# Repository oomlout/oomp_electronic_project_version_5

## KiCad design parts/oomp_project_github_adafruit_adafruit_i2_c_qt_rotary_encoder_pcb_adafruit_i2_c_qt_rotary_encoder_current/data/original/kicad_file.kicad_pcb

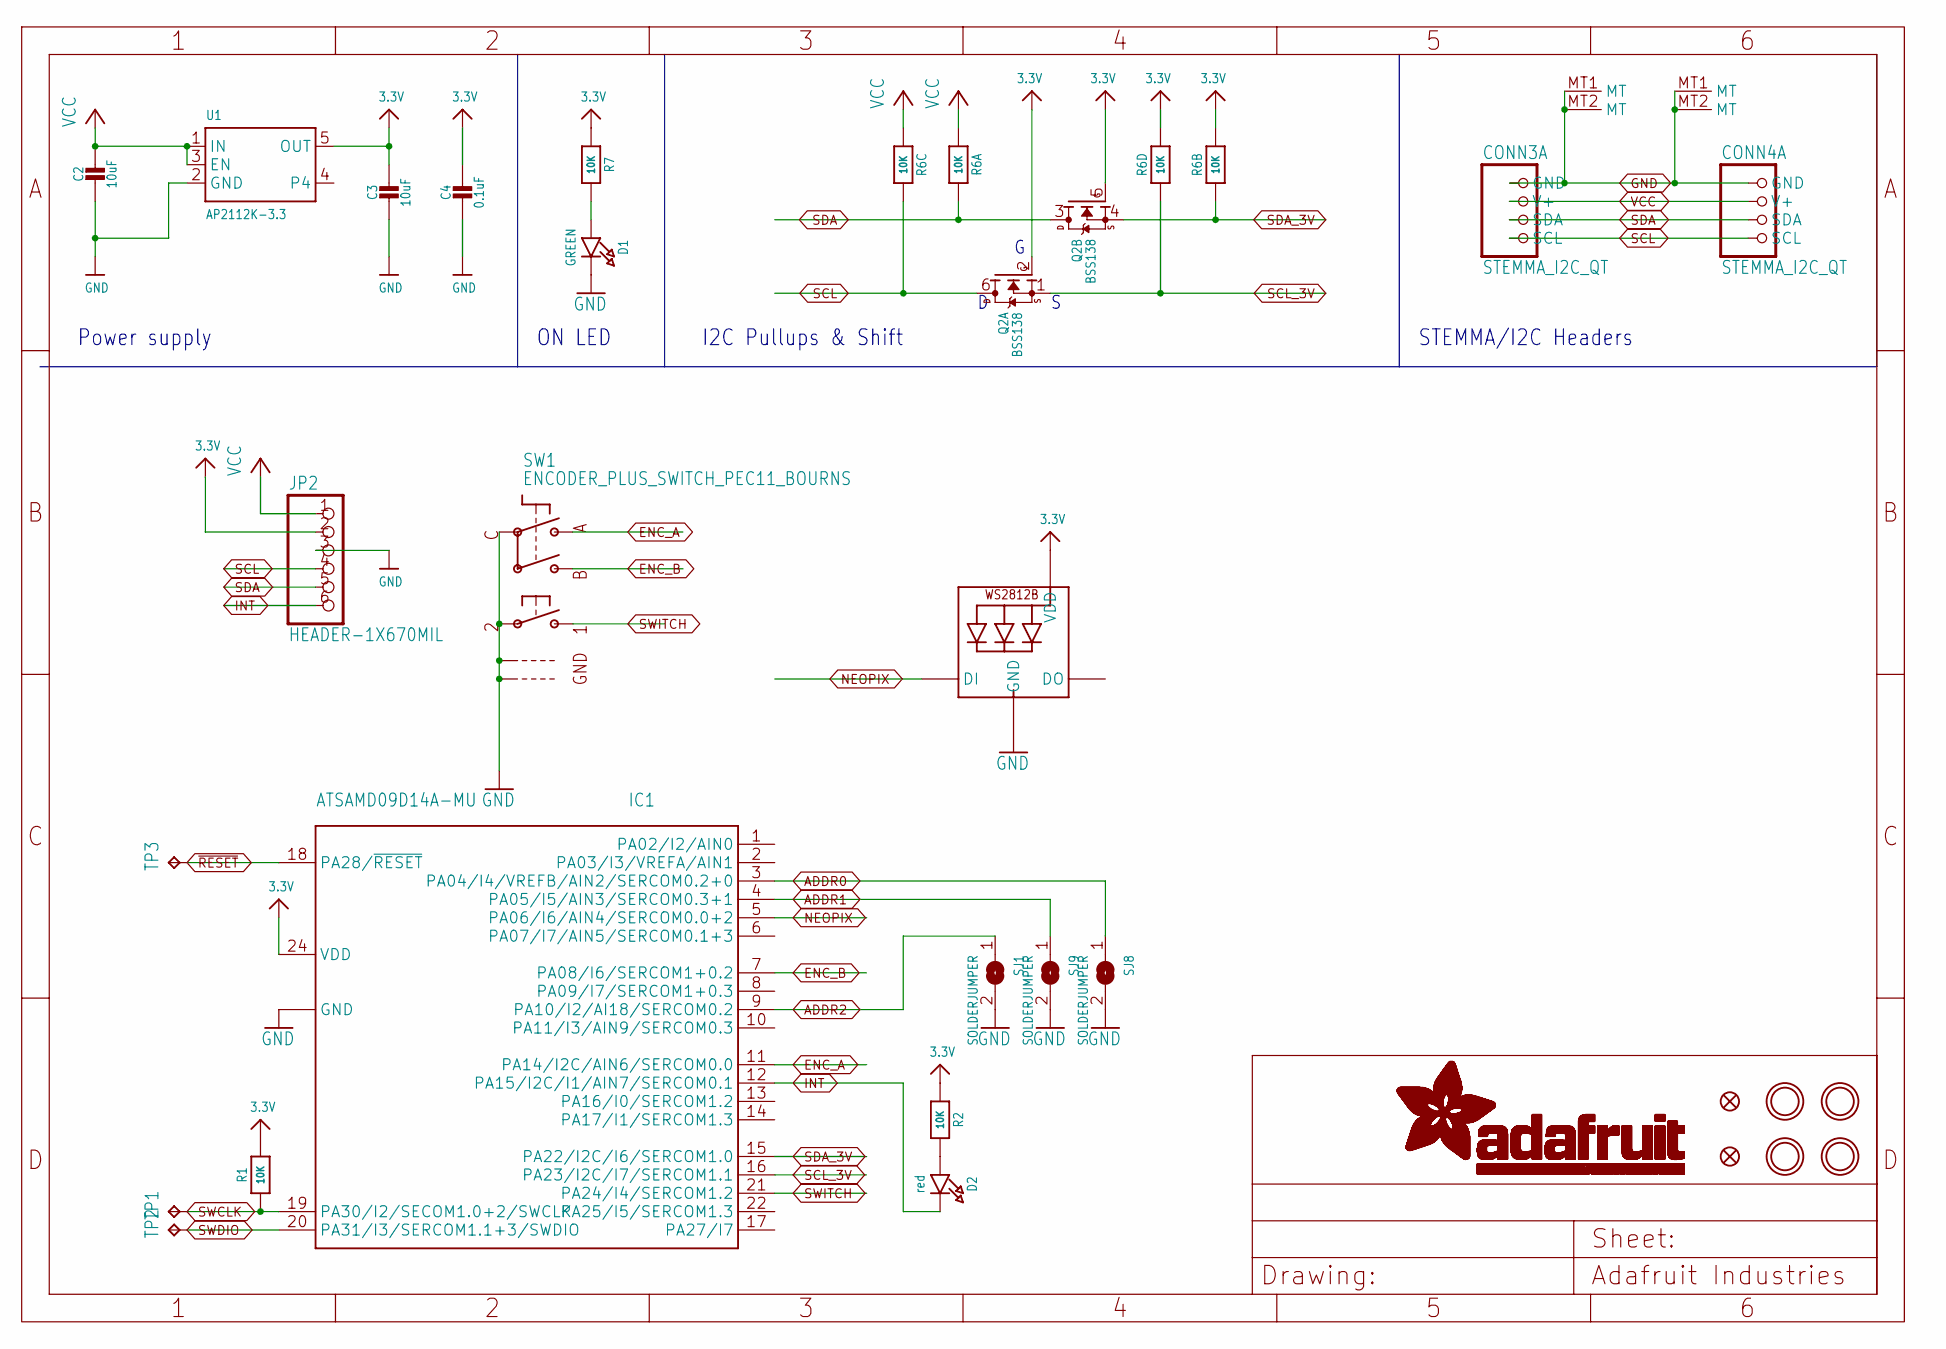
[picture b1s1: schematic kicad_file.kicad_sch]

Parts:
C2, C3: 10uF; 0805-NO
C4: 0.1uF; 0603-NO
CONN3, CONN4: STEMMA_I2C_QT; JST_SH4
D1: GREEN; CHIPLED_0603_NOOUTLINE
D2: red; CHIPLED_0603_NOOUTLINE
FID3, FID4: FIDUCIAL_1MM
IC1: ATSAMD09D14A-MU; QFN24_4MM
JP2: HEADER-1X670MIL; 1X06_ROUND_70
LED1: WS2812B_SK6812E; NEO3535_REVERSE
Q2: BSS138; SOT363
R1, R2, R7: 10K; 0603-NO
R6: 10K; RESPACK_4X0603
SJ1, SJ8, SJ9: SOLDERJUMPER; SOLDERJUMPER_ARROW_NOPASTE
SW1: ENCODER_PLUS_SWITCH_PEC11_BOURNS; PEC11+SWITCH
TP1, TP2, TP3: TPTP15R; TP15R
U1: AP2112K-3.3; SOT23-5
U$25, U$27, U$29, U$30: MOUNTINGHOLE2.5; MOUNTINGHOLE_2.5_PLATED

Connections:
3.3V: C3.1, C4.1, IC1.24 (VDD), JP2.2, LED1.1-VDD (VDD), Q2.2 (G), Q2.5 (G), R1.2, R2.1, R6.2 (1), R6.4 (1), R7.1, U1.5 (OUT)
ADDR0: IC1.3 (PA04/I4/VREFB/AIN2/SERCOM0.2+0), SJ8.1
ADDR1: IC1.4 (PA05/I5/AIN3/SERCOM0.3+1), SJ9.1
ADDR2: IC1.9 (PA10/I2/AI18/SERCOM0.2), SJ1.1
ENC_A: IC1.11 (PA14/I2C/AIN6/SERCOM0.0), SW1.P$A
ENC_B: IC1.7 (PA08/I6/SERCOM1+0.2), SW1.P$B
GND: C2.2, C3.2, C4.2, CONN3.1 (GND), CONN3.MT1 (MT), CONN3.MT2 (MT), CONN4.1 (GND), CONN4.MT1 (MT), CONN4.MT2 (MT), D1.C, IC1.23 (GND), IC1.THERM (GND), JP2.3, LED1.3-GND (GND), SJ1.2, SJ8.2, SJ9.2, SW1.P$2, SW1.P$C, SW1.P$GND1, SW1.P$GND2, U1.2 (GND)
INT: D2.C, IC1.12 (PA15/I2C/I1/AIN7/SERCOM0.1), JP2.6
unnamed: D1.A, R7.2
unnamed: D2.A, R2.2
NEOPIX: IC1.5 (PA06/I6/AIN4/SERCOM0.0+2), LED1.4-DIN (DI)
SCL: CONN3.4 (SCL), CONN4.4 (SCL), JP2.4, Q2.6 (D), R6.6 (2)
SCL_3V: IC1.16 (PA23/I2C/I7/SERCOM1.1), Q2.1 (S), R6.5 (2)
SDA: CONN3.3 (SDA), CONN4.3 (SDA), JP2.5, Q2.3 (D), R6.8 (2)
SDA_3V: IC1.15 (PA22/I2C/I6/SERCOM1.0), Q2.4 (S), R6.7 (2)
SWCLK: IC1.19 (PA30/I2/SECOM1.0+2/SWCLK), R1.1, TP1.TP
SWDIO: IC1.20 (PA31/I3/SERCOM1.1+3/SWDIO), TP2.TP
SWITCH: IC1.21 (PA24/I4/SERCOM1.2), SW1.P$1
VCC: C2.1, CONN3.2 (V+), CONN4.2 (V+), JP2.1, R6.1, R6.3 (1), U1.1 (IN), U1.3 (EN)
~RESET: IC1.18 (PA28/~RESET), TP3.TP

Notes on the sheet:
Power supply
I2C Pullups & Shift
ON LED
STEMMA/I2C Headers

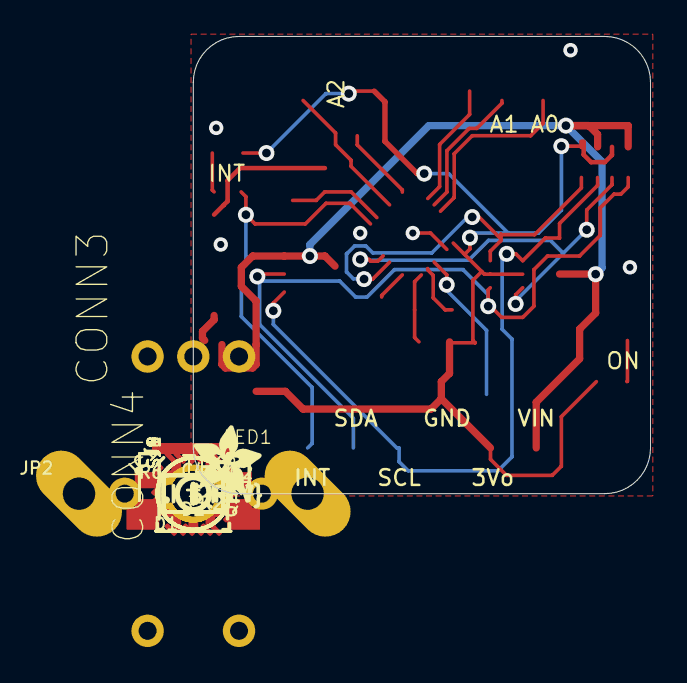
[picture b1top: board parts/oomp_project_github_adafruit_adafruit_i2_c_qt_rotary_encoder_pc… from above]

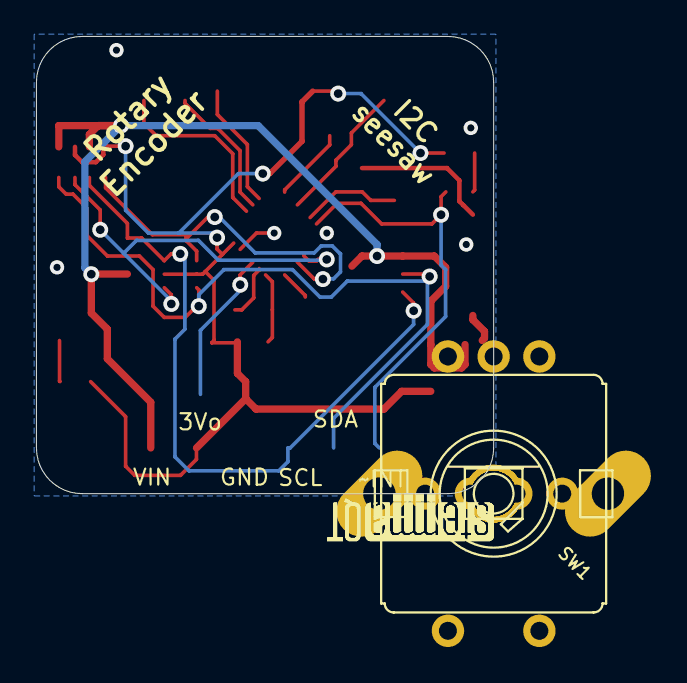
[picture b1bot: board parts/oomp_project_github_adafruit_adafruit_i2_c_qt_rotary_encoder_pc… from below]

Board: 2 copper layers, 25.4 x 25.4 mm, 33 parts (4 on the bottom side), 20 nets.

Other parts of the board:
U$32: ADAFRUIT_3.5MM
U$33: PCBFEAT-REV-040
U$34, U$35: STEMMAQT

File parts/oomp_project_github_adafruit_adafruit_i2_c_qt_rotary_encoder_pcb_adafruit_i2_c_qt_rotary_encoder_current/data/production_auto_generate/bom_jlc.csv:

Comment,Designator,Footprint,LCSC Part #
,JP2,Adafruit I2C QT Rotary Encoder-import-fps:1X06_ROUND_70,C37208
,U$32,Adafruit I2C QT Rotary Encoder-import-fps:ADAFRUIT_3.5MM,
,U$33,Adafruit I2C QT Rotary Encoder-import-fps:PCBFEAT-REV-040,
,"U$34,U$35",Adafruit I2C QT Rotary Encoder-import-fps:STEMMAQT,
0.1uF,C4,Adafruit I2C QT Rotary Encoder-import-fps:0603-NO,C14663
10K,"R1,R2,R7",Adafruit I2C QT Rotary Encoder-import-fps:0603-NO,C98220
10K,R6,Adafruit I2C QT Rotary Encoder-import-fps:RESPACK_4X0603,C98220
10uF,"C2,C3",Adafruit I2C QT Rotary Encoder-import-fps:0805-NO,
AP2112K-3.3,U1,Adafruit I2C QT Rotary Encoder-import-fps:SOT23-5,
ATSAMD09D14A-MU,IC1,Adafruit I2C QT Rotary Encoder-import-fps:QFN24_4MM,
BSS138,Q2,Adafruit I2C QT Rotary Encoder-import-fps:SOT363,
GREEN,D1,Adafruit I2C QT Rotary Encoder-import-fps:CHIPLED_0603_NOOUTLINE,
red,D2,Adafruit I2C QT Rotary Encoder-import-fps:CHIPLED_0603_NOOUTLINE,
STEMMA_I2C_QT,"CONN3,CONN4",Adafruit I2C QT Rotary Encoder-import-fps:JST_SH4,C160404
TPTP15R,"TP1,TP2,TP3",Adafruit I2C QT Rotary Encoder-import-fps:TP15R,
WS2812B_SK6812E,LED1,Adafruit I2C QT Rotary Encoder-import-fps:NEO3535_REVERSE,

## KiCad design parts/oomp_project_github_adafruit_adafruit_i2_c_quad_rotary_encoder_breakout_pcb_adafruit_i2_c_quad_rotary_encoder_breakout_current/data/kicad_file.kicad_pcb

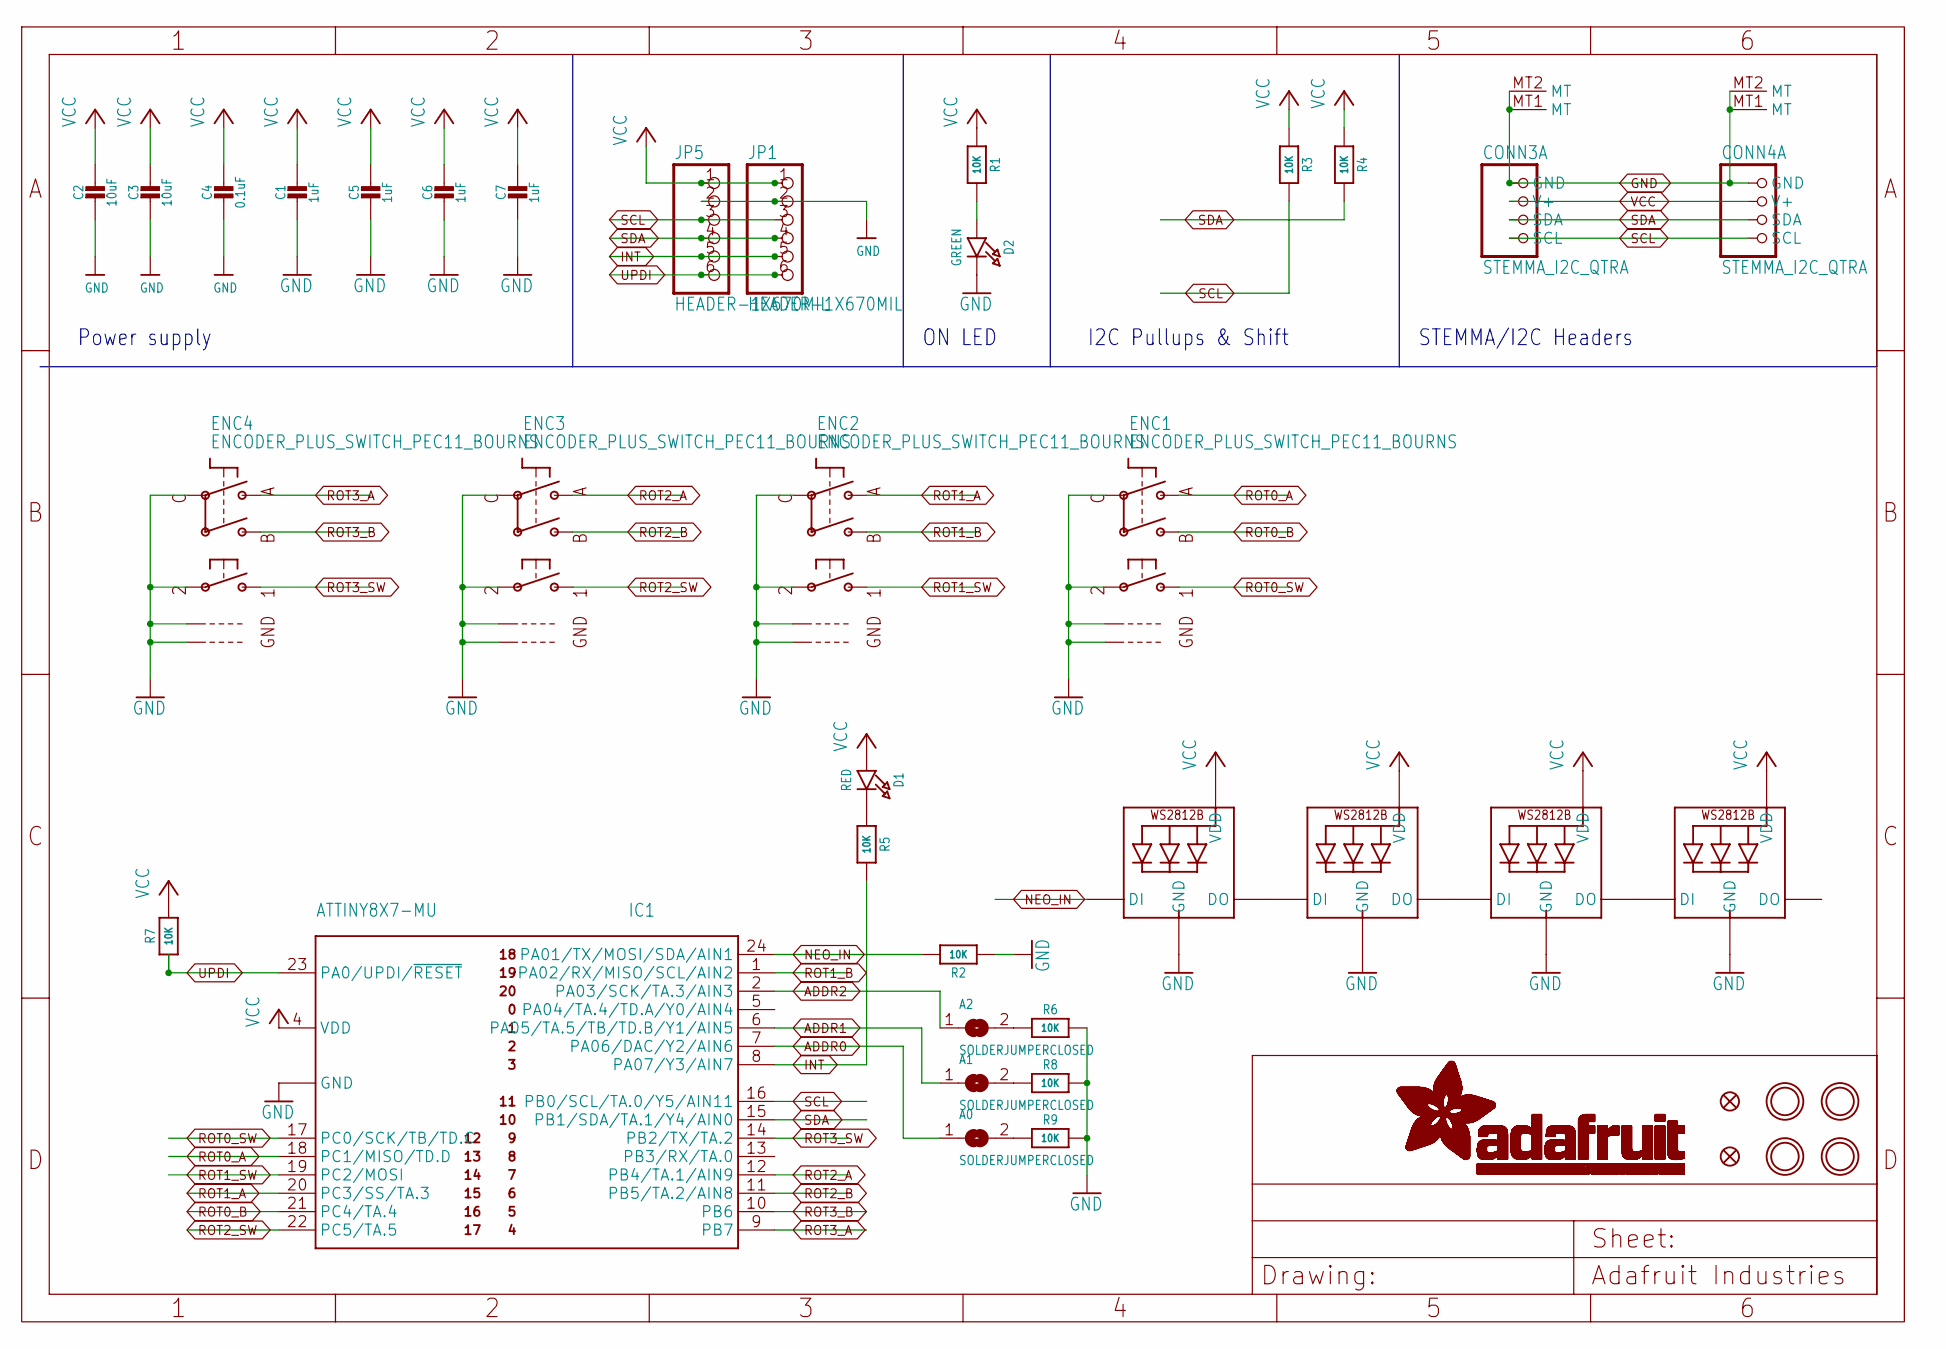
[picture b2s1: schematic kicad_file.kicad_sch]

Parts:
A0, A1, A2: SOLDERJUMPERCLOSED; SOLDERJUMPER_CLOSEDWIRE
C1, C5, C6, C7: 1uF; 0603-NO
C2, C3: 10uF; 0805-NO
C4: 0.1uF; 0603-NO
CONN3, CONN4: STEMMA_I2C_QTRA; JST_SH4_RA; LCSC C145961
D1: RED; CHIPLED_0603_NOOUTLINE
D2: GREEN; CHIPLED_0603_NOOUTLINE
ENC1, ENC2, ENC3, ENC4: ENCODER_PLUS_SWITCH_PEC11_BOURNS; PEC11+SWITCH
FID1, FID2: FIDUCIAL_1MM
IC1: ATTINY8X7-MU; QFN24_4MM
JP1, JP5: HEADER-1X670MIL; 1X06_ROUND_70
LED1, LED2, LED3, LED4: WS2812B_SK6812E; NEO3535_REVERSE
R1, R2, R3, R4, R5, R6, R7, R8, R9: 10K; 0603-NO
U$3, U$17, U$19, U$21: MOUNTINGHOLE2.5; MOUNTINGHOLE_2.5_PLATED

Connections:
ADDR0: A0.1, IC1.7 (PA06/DAC/Y2/AIN6)
ADDR1: A1.1, IC1.6 (PA05/TA.5/TB/TD.B/Y1/AIN5)
ADDR2: A2.1, IC1.2 (PA03/SCK/TA.3/AIN3)
GND: C1.2, C2.2, C3.2, C4.2, C5.2, C6.2, C7.2, CONN3.1 (GND), CONN3.MT1 (MT), CONN3.MT2 (MT), CONN4.1 (GND), CONN4.MT1 (MT), CONN4.MT2 (MT), D2.C, ENC1.P$2, ENC1.P$C, ENC1.P$GND1, ENC1.P$GND2, ENC2.P$2, ENC2.P$C, ENC2.P$GND1, ENC2.P$GND2, ENC3.P$2, ENC3.P$C, ENC3.P$GND1, ENC3.P$GND2, ENC4.P$2, ENC4.P$C, ENC4.P$GND1, ENC4.P$GND2, IC1.3 (GND), IC1.THERM (GND), JP1.2, JP5.2, LED1.3-GND (GND), LED2.3-GND (GND), LED3.3-GND (GND), LED4.3-GND (GND), R2.1, R6.2, R8.2, R9.2
INT: IC1.8 (PA07/Y3/AIN7), JP1.5, JP5.5, R5.2
unnamed: D2.A, R1.2
unnamed: LED1.2-DOUT (DO), LED2.4-DIN (DI)
unnamed: LED2.2-DOUT (DO), LED3.4-DIN (DI)
unnamed: LED3.2-DOUT (DO), LED4.4-DIN (DI)
unnamed: D1.C, R5.1
unnamed: A2.2, R6.1
unnamed: A1.2, R8.1
unnamed: A0.2, R9.1
NEO_IN: IC1.24 (PA01/TX/MOSI/SDA/AIN1), LED1.4-DIN (DI), R2.2
ROT0_A: ENC1.P$A, IC1.18 (PC1/MISO/TD.D)
ROT0_B: ENC1.P$B, IC1.21 (PC4/TA.4)
ROT0_SW: ENC1.P$1, IC1.17 (PC0/SCK/TB/TD.C)
ROT1_A: ENC2.P$A, IC1.20 (PC3/SS/TA.3)
ROT1_B: ENC2.P$B, IC1.1 (PA02/RX/MISO/SCL/AIN2)
ROT1_SW: ENC2.P$1, IC1.19 (PC2/MOSI)
ROT2_A: ENC3.P$A, IC1.12 (PB4/TA.1/AIN9)
ROT2_B: ENC3.P$B, IC1.11 (PB5/TA.2/AIN8)
ROT2_SW: ENC3.P$1, IC1.22 (PC5/TA.5)
ROT3_A: ENC4.P$A, IC1.9 (PB7)
ROT3_B: ENC4.P$B, IC1.10 (PB6)
ROT3_SW: ENC4.P$1, IC1.14 (PB2/TX/TA.2)
SCL: CONN3.4 (SCL), CONN4.4 (SCL), IC1.16 (PB0/SCL/TA.0/Y5/AIN11), JP1.3, JP5.3, R3.2
SDA: CONN3.3 (SDA), CONN4.3 (SDA), IC1.15 (PB1/SDA/TA.1/Y4/AIN0), JP1.4, JP5.4, R4.2
UPDI: IC1.23 (PA0/UPDI/~RESET), JP1.6, JP5.6, R7.1
VCC: C1.1, C2.1, C3.1, C4.1, C5.1, C6.1, C7.1, CONN3.2 (V+), CONN4.2 (V+), D1.A, IC1.4 (VDD), JP1.1, JP5.1, LED1.1-VDD (VDD), LED2.1-VDD (VDD), LED3.1-VDD (VDD), LED4.1-VDD (VDD), R1.1, R3.1, R4.1, R7.2

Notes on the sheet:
I2C Pullups & Shift
Power supply
STEMMA/I2C Headers
ON LED

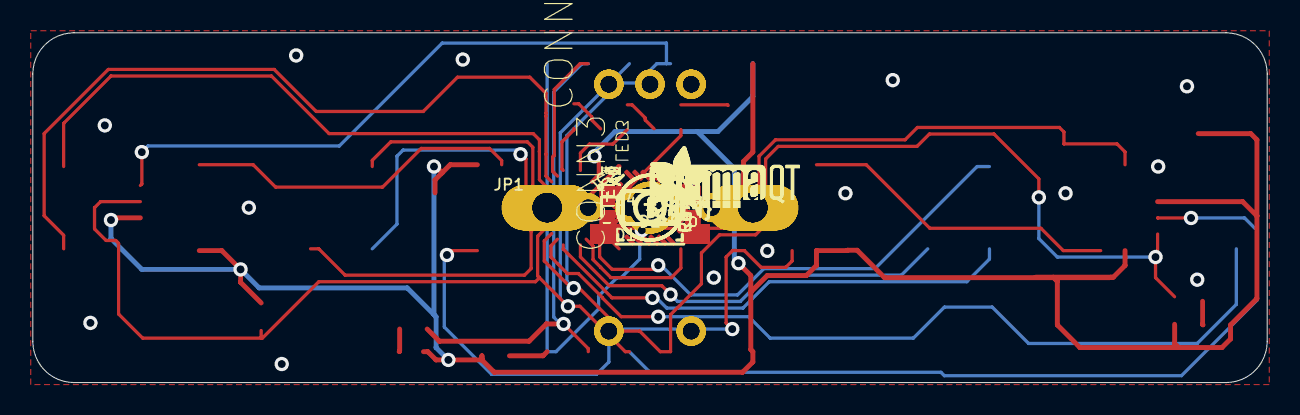
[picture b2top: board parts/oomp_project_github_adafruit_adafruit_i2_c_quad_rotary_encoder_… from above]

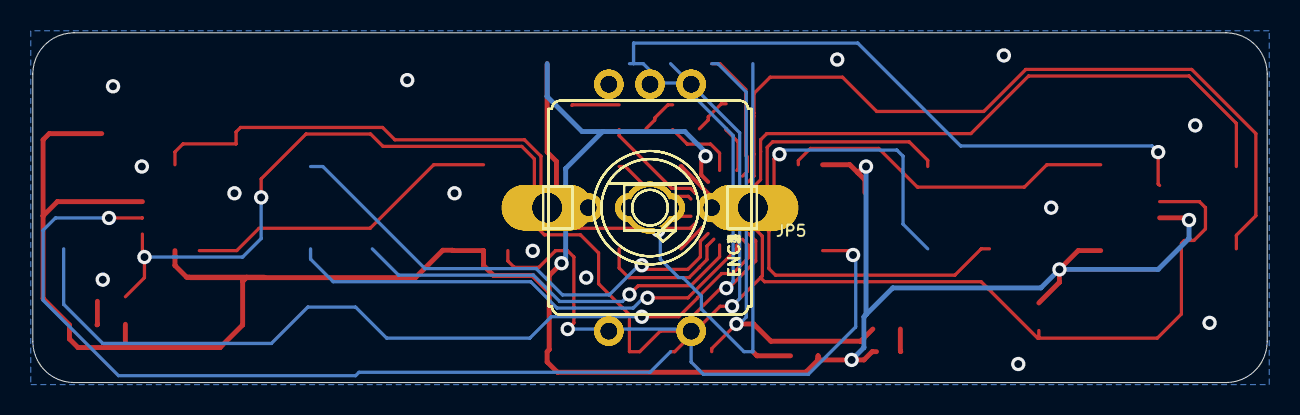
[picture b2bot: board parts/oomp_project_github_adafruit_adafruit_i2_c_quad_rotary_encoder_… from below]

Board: 2 copper layers, 76.2 x 21.6 mm, 78 parts (25 on the bottom side), 30 nets.

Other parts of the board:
PLABEL0: PLABEL0
PLABEL1: PLABEL1
PLABEL2: PLABEL2
PLABEL3: PLABEL3
PLABEL4: PLABEL4
PLABEL5: PLABEL5
PLABEL6: PLABEL6
PLABEL7: PLABEL7
PLABEL8: PLABEL8
PLABEL9: PLABEL9
PLABEL10: PLABEL10
PLABEL11: PLABEL11
PLABEL12: PLABEL12
PLABEL13: PLABEL13
PLABEL14: PLABEL14
PLABEL15: PLABEL15
PLABEL16: PLABEL16
PLABEL17: PLABEL17
PLABEL18: PLABEL18
PLABEL19: PLABEL19
PLABEL20: PLABEL20
PLABEL21: PLABEL21
PLABEL22: PLABEL22
PLABEL23: PLABEL23
PLABEL24: PLABEL24
PLABEL25: PLABEL25
PLABEL26: PLABEL26
PLABEL27: PLABEL27
PLABEL28: PLABEL28
PLABEL29: PLABEL29
PLABEL30: PLABEL30
PLABEL31: PLABEL31
PLABEL32: PLABEL32
U$2, U$9: ADAFRUIT_3.5MM
U$25: PCBFEAT-REV-040
U$30, U$31: STEMMAQT

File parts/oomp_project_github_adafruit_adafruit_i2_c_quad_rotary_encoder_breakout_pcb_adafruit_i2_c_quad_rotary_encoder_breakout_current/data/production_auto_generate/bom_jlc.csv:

Comment,Designator,Footprint,LCSC Part #
,"JP1,JP5",Adafruit I2C Quad Rotary Encoder Breakout-import-fps:1X06_ROUND_70,C37208
,"U$2,U$9",Adafruit I2C Quad Rotary Encoder Breakout-import-fps:ADAFRUIT_3.5MM,
,U$25,Adafruit I2C Quad Rotary Encoder Breakout-import-fps:PCBFEAT-REV-040,
,PLABEL0,Adafruit I2C Quad Rotary Encoder Breakout-import-fps:PLABEL0,
,PLABEL1,Adafruit I2C Quad Rotary Encoder Breakout-import-fps:PLABEL1,
,PLABEL10,Adafruit I2C Quad Rotary Encoder Breakout-import-fps:PLABEL10,
,PLABEL11,Adafruit I2C Quad Rotary Encoder Breakout-import-fps:PLABEL11,
,PLABEL12,Adafruit I2C Quad Rotary Encoder Breakout-import-fps:PLABEL12,
,PLABEL13,Adafruit I2C Quad Rotary Encoder Breakout-import-fps:PLABEL13,
,PLABEL14,Adafruit I2C Quad Rotary Encoder Breakout-import-fps:PLABEL14,
,PLABEL15,Adafruit I2C Quad Rotary Encoder Breakout-import-fps:PLABEL15,
,PLABEL16,Adafruit I2C Quad Rotary Encoder Breakout-import-fps:PLABEL16,
,PLABEL17,Adafruit I2C Quad Rotary Encoder Breakout-import-fps:PLABEL17,
,PLABEL18,Adafruit I2C Quad Rotary Encoder Breakout-import-fps:PLABEL18,
,PLABEL19,Adafruit I2C Quad Rotary Encoder Breakout-import-fps:PLABEL19,
,PLABEL2,Adafruit I2C Quad Rotary Encoder Breakout-import-fps:PLABEL2,
,PLABEL20,Adafruit I2C Quad Rotary Encoder Breakout-import-fps:PLABEL20,
,PLABEL21,Adafruit I2C Quad Rotary Encoder Breakout-import-fps:PLABEL21,
,PLABEL22,Adafruit I2C Quad Rotary Encoder Breakout-import-fps:PLABEL22,
,PLABEL23,Adafruit I2C Quad Rotary Encoder Breakout-import-fps:PLABEL23,
,PLABEL24,Adafruit I2C Quad Rotary Encoder Breakout-import-fps:PLABEL24,
,PLABEL25,Adafruit I2C Quad Rotary Encoder Breakout-import-fps:PLABEL25,
,PLABEL26,Adafruit I2C Quad Rotary Encoder Breakout-import-fps:PLABEL26,
,PLABEL27,Adafruit I2C Quad Rotary Encoder Breakout-import-fps:PLABEL27,
,PLABEL28,Adafruit I2C Quad Rotary Encoder Breakout-import-fps:PLABEL28,
,PLABEL29,Adafruit I2C Quad Rotary Encoder Breakout-import-fps:PLABEL29,
,PLABEL3,Adafruit I2C Quad Rotary Encoder Breakout-import-fps:PLABEL3,
,PLABEL30,Adafruit I2C Quad Rotary Encoder Breakout-import-fps:PLABEL30,
,PLABEL31,Adafruit I2C Quad Rotary Encoder Breakout-import-fps:PLABEL31,
,PLABEL32,Adafruit I2C Quad Rotary Encoder Breakout-import-fps:PLABEL32,
,PLABEL4,Adafruit I2C Quad Rotary Encoder Breakout-import-fps:PLABEL4,
,PLABEL5,Adafruit I2C Quad Rotary Encoder Breakout-import-fps:PLABEL5,
,PLABEL6,Adafruit I2C Quad Rotary Encoder Breakout-import-fps:PLABEL6,
,PLABEL7,Adafruit I2C Quad Rotary Encoder Breakout-import-fps:PLABEL7,
,PLABEL8,Adafruit I2C Quad Rotary Encoder Breakout-import-fps:PLABEL8,
,PLABEL9,Adafruit I2C Quad Rotary Encoder Breakout-import-fps:PLABEL9,
,"A0,A1,A2",Adafruit I2C Quad Rotary Encoder Breakout-import-fps:SOLDERJUMPER_CLOSEDWIRE,
,"U$30,U$31",Adafruit I2C Quad Rotary Encoder Breakout-import-fps:STEMMAQT,
0.1uF,C4,Adafruit I2C Quad Rotary Encoder Breakout-import-fps:0603-NO,C14663
10K,"R1,R2,R3,R4,R5,R6,R7,R8,R9",Adafruit I2C Quad Rotary Encoder Breakout-import-fps:0603-NO,C98220
10uF,"C2,C3",Adafruit I2C Quad Rotary Encoder Breakout-import-fps:0805-NO,
1uF,"C1,C5,C6,C7",Adafruit I2C Quad Rotary Encoder Breakout-import-fps:0603-NO,C5673
ATTINY8X7-MU,IC1,Adafruit I2C Quad Rotary Encoder Breakout-import-fps:QFN24_4MM,
GREEN,D2,Adafruit I2C Quad Rotary Encoder Breakout-import-fps:CHIPLED_0603_NOOUTLINE,
RED,D1,Adafruit I2C Quad Rotary Encoder Breakout-import-fps:CHIPLED_0603_NOOUTLINE,
STEMMA_I2C_QTRA,"CONN3,CONN4",Adafruit I2C Quad Rotary Encoder Breakout-import-fps:JST_SH4_RA,
WS2812B_SK6812E,"LED1,LED2,LED3,LED4",Adafruit I2C Quad Rotary Encoder Breakout-import-fps:NEO3535_REVERSE,

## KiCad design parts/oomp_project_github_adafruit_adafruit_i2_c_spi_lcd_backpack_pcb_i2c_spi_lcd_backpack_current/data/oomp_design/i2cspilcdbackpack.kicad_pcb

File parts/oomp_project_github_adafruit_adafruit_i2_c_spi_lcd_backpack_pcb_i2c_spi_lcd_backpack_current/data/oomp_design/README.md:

# OOMP KiCad design copy

Open `i2cspilcdbackpack.kicad_pro` (or the `.kicad_pcb` / `.kicad_sch`) in KiCad. Local OOMP libraries are under `libraries/`. Original inputs are preserved in [../original/](../original/).

Only verified unchanged installed KiCad defaults were renamed. Modified, custom, unmatched and unavailable items remain unchanged. Soldering variants are never swapped during conversion. Existing pad coordinates, nets and UUIDs are preserved.

See [conversion_report.yaml](conversion_report.yaml) for every conversion and skip. Copy this directory before editing; regeneration refuses to overwrite edited design files.

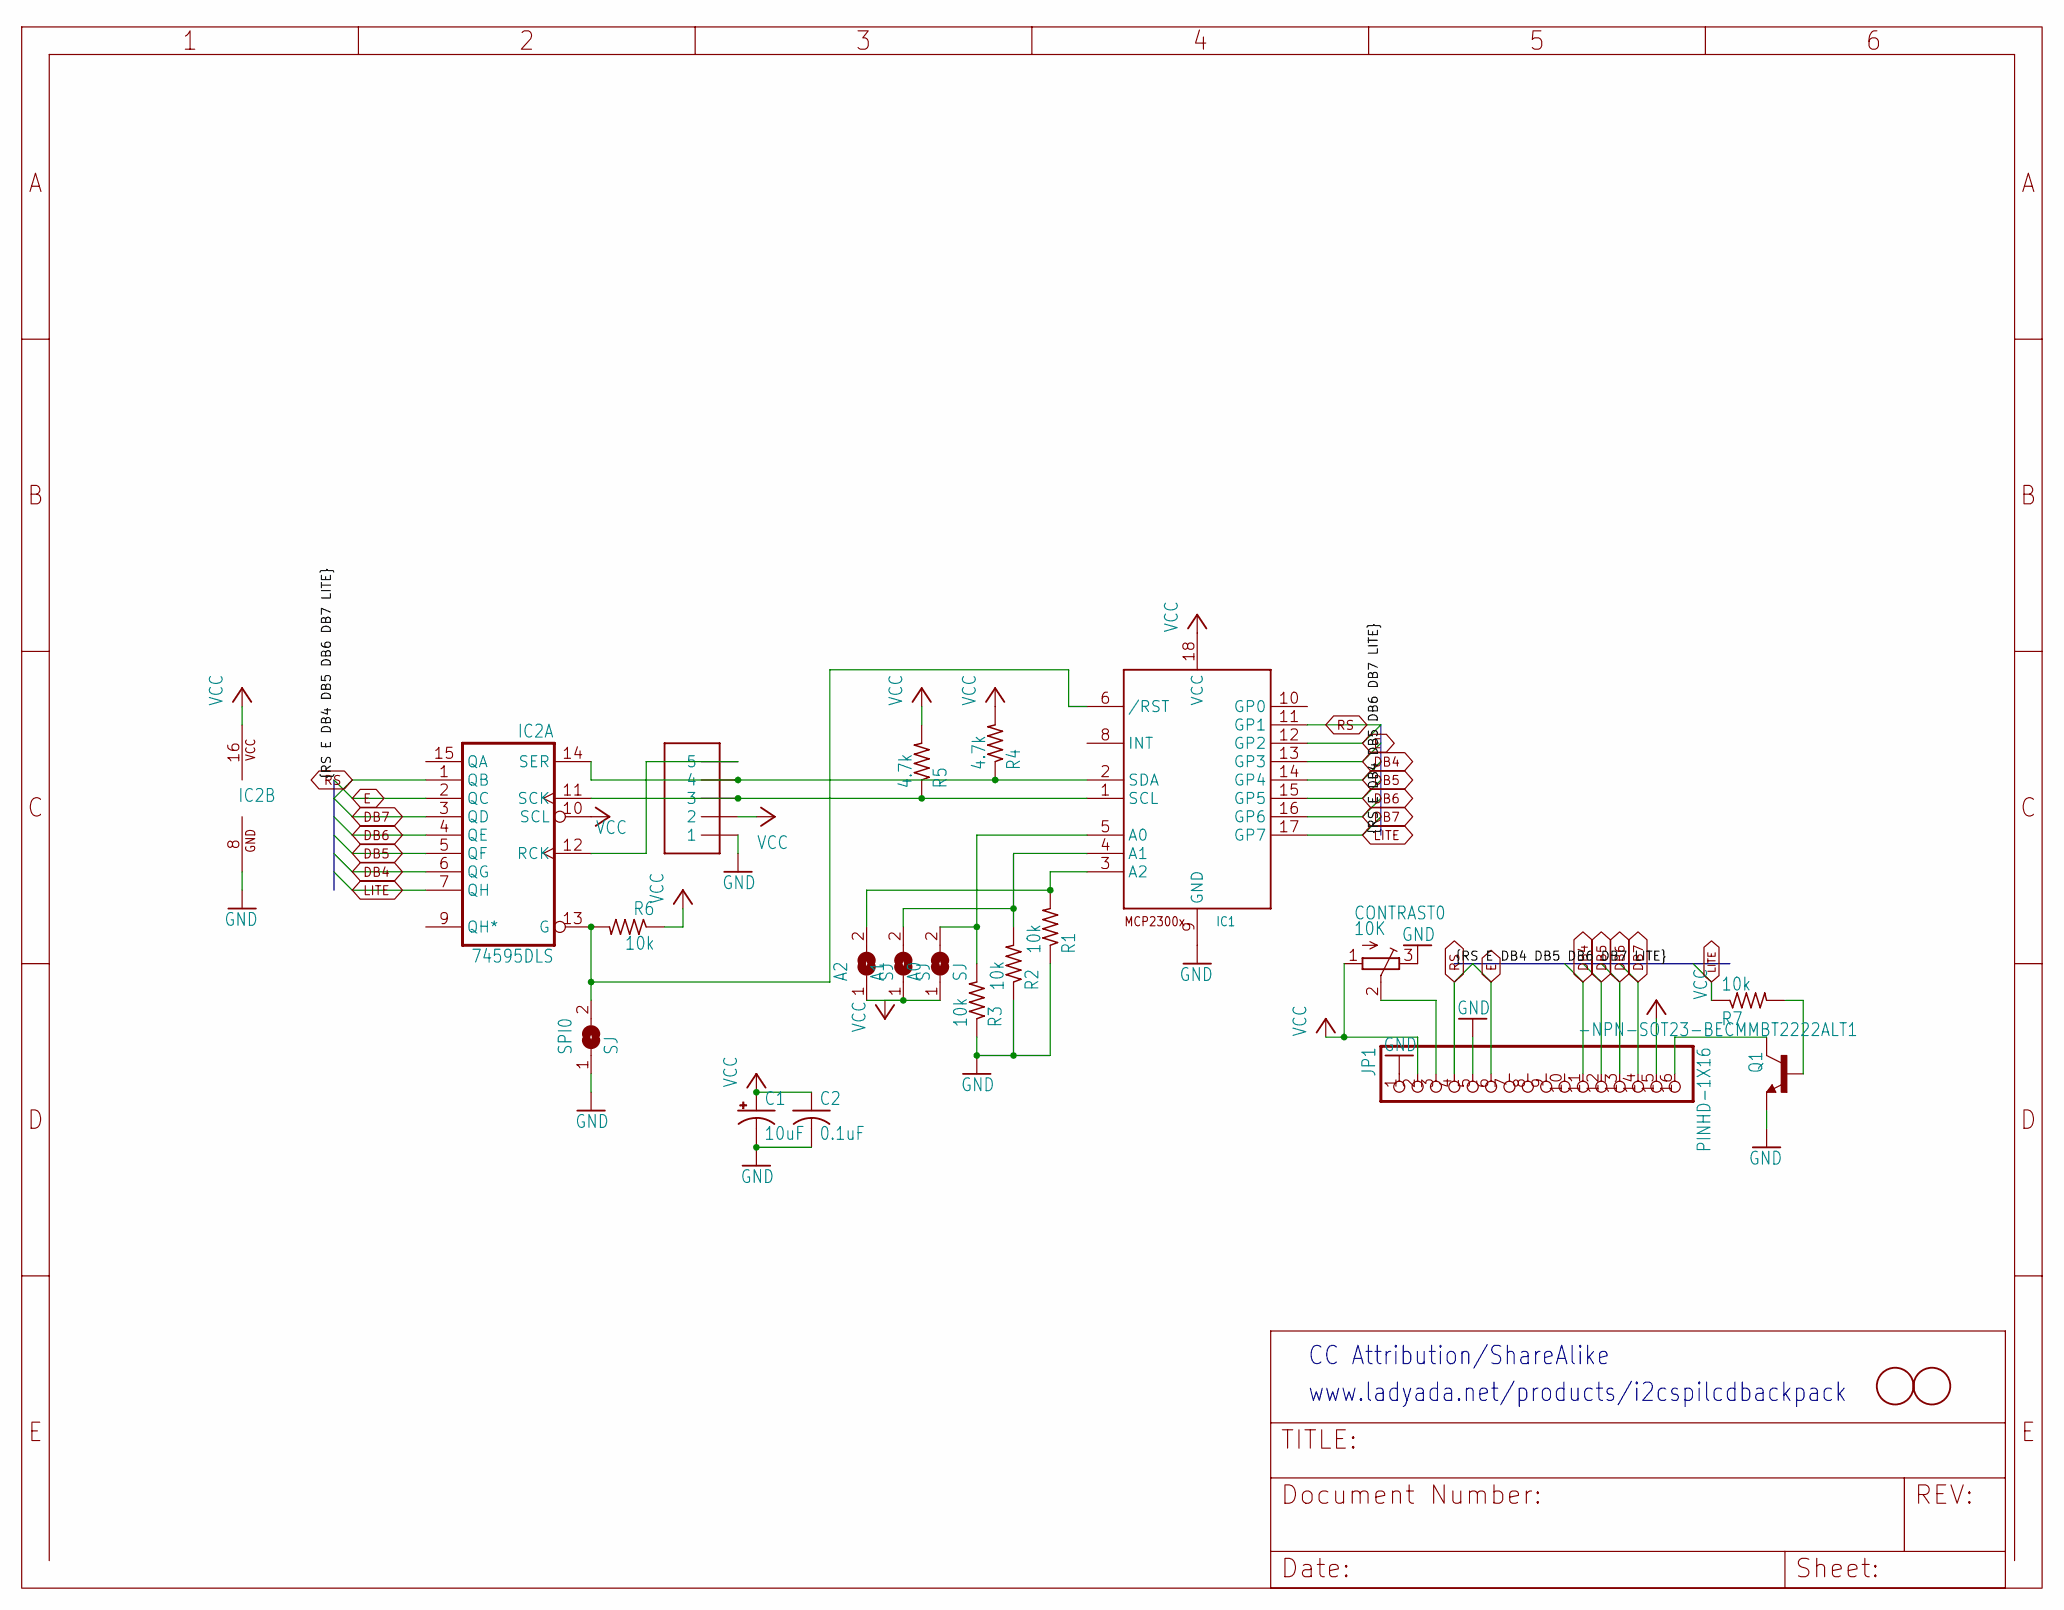
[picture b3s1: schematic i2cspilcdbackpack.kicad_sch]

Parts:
A0, A1, A2: SJ
C1: 10uF; A_3216-18R
C2: 0.1uF; C0805K
CONTRAST0: 10K; TC33X
IC1: MCP2300X/SO; SO18W
IC2: 74595DLS; SO16
J1: 1X5; 3.5MM-5P
JP1: PINHD-1X16; 1X16
Q1: -NPN-SOT23-BECMMBT2222ALT1; SOT23-BEC
R1, R2, R3, R6, R7: 10k; R0805
R4, R5: 4.7k; R0805
SPI0: SJ
U$1, U$2: FIDUCIAL; FIDUCIAL_1MM

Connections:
CLOCK: IC1.1 (SCL), IC2.11 (SCK), J1.3, R5.1
DATA: IC1.2 (SDA), IC2.14 (SER), J1.4, R4.1
DB4: IC1.13 (GP3), IC2.6 (QG), JP1.11
DB5: IC1.14 (GP4), IC2.5 (QF), JP1.12
DB6: IC1.15 (GP5), IC2.4 (QE), JP1.13
DB7: IC1.16 (GP6), IC2.3 (QD), JP1.14
E: IC1.12 (GP2), IC2.2 (QC), JP1.6
GND: C1.-, C2.2, CONTRAST0.3 (E), IC1.9 (GND), IC2.8 (GND), J1.1, JP1.1, JP1.5, Q1.E, R1.1, R2.1, R3.1, SPI0.1
LATCH: IC2.12 (RCK), J1.5
LITE: IC1.17 (GP7), IC2.7 (QH), R7.1
unnamed: A0.2, IC1.5 (A0), R3.2
unnamed: A1.2, IC1.4 (A1), R2.2
unnamed: A2.2, IC1.3 (A2), R1.2
unnamed: IC1.6 (/RST), IC2.13 (G), R6.2, SPI0.2
unnamed: JP1.16, Q1.C
unnamed: Q1.B, R7.2
unnamed: CONTRAST0.2 (S), JP1.3
RS: IC1.11 (GP1), IC2.1 (QB), JP1.4
VCC: A0.1, A1.1, A2.1, C1.+, C2.1, CONTRAST0.1 (A), IC1.18 (VCC), IC2.10 (SCL), IC2.16 (VCC), J1.2, JP1.2, JP1.15, R4.2, R5.2, R6.1

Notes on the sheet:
www.ladyada.net/products/i2cspilcdbackpack
CC Attribution/ShareAlike

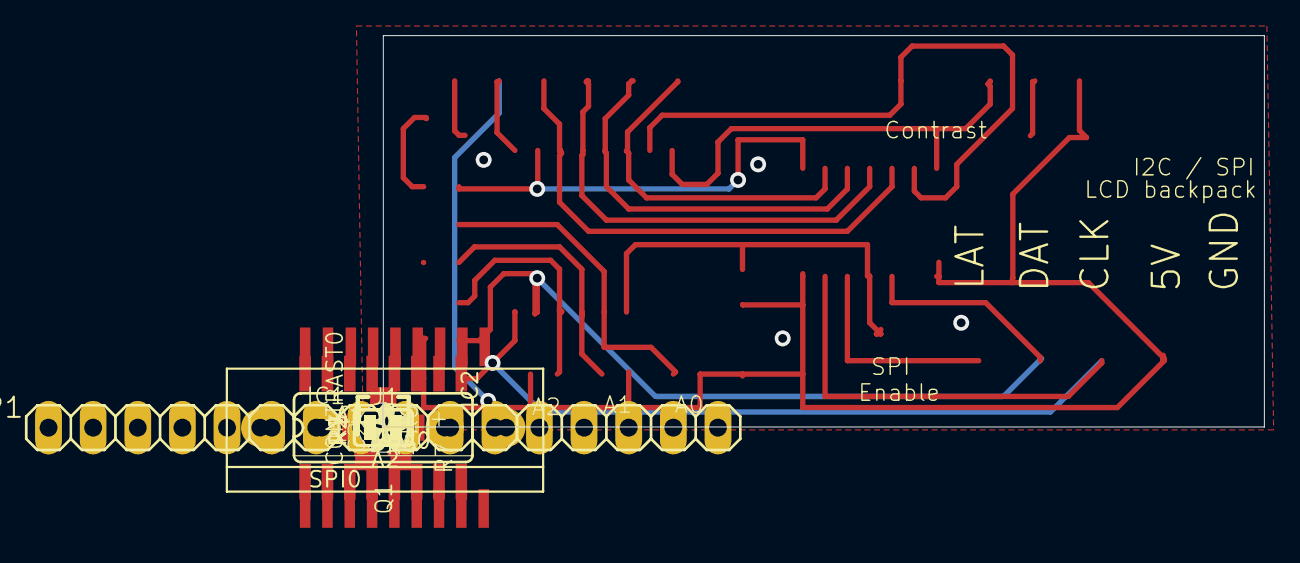
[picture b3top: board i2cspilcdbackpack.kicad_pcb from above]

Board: 16 copper layers, 50.1 x 22.3 mm, 23 parts (0 on the bottom side), 19 nets.

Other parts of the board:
U$3: ADAFRUIT200MIL
UNK_HOLE_0: dummyfp0

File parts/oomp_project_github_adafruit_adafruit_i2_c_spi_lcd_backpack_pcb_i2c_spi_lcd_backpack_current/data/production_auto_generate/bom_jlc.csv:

Comment,Designator,Footprint,LCSC Part #
,JP1,i2cspilcdbackpack-import-fps:1X16,C7501270
,U$3,i2cspilcdbackpack-import-fps:ADAFRUIT200MIL,
,"A0,A1,A2,SPI0",i2cspilcdbackpack-import-fps:SJ,
,Q1,i2cspilcdbackpack-import-fps:SOT23-BEC,
0.1uF,C2,i2cspilcdbackpack-import-fps:C0805K,
10k,"R1,R2,R3,R6,R7",i2cspilcdbackpack-import-fps:R0805,C17414
10K,CONTRAST0,i2cspilcdbackpack-import-fps:TC33X,
10uF,C1,i2cspilcdbackpack-import-fps:A_3216-18R,
1X5,J1,i2cspilcdbackpack-import-fps:3.5MM-5P,
4.7k,"R4,R5",i2cspilcdbackpack-import-fps:R0805,C2907264
74LS595D,IC2,i2cspilcdbackpack-import-fps:SO16,
FIDUCIAL,"U$1,U$2",i2cspilcdbackpack-import-fps:FIDUCIAL_1MM,
MCP2300X/SO,IC1,i2cspilcdbackpack-import-fps:SO18W,
